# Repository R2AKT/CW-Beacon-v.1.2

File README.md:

# CW_Beacon
2-х канальный QPR CW автономный маяк (возможна работа только одного канала).
В основе Arduino Nano, генераторная часть построена на кварцевом резонаторе
и стандартной логике. В качестве оконечного каскада используется магистральный
шинный формирователь. На выходе стоят ФНЧ 7-го порядка.

Маяк передаёт заранее заложенное сообщение, при наличии термодатчика DS18B20 и/или резистивного 
делителя напряжения можно добавлять измеренные значения в сообщение.

Подробное описание можно найти на сайте <a href="https://r2akt.ru/%d0%bf%d1%80%d0%be%d0%b5%d0%ba%d1%82%d1%8b/%d0%b0%d0%b2%d1%82%d0%be%d0%bd%d0%be%d0%bc%d0%bd%d1%8b%d0%b9-cw-%d0%bc%d0%b0%d1%8f%d0%ba-%d0%bd%d0%b0-%d0%b1%d0%b0%d0%b7%d0%b5-arduino-nano/" target=_blank>https://r2akt.ru/%d0%bf%d1%80%d0%be%d0%b5%d0%ba%d1%82%d1%8b/%d0%b0%d0%b2%d1%82%d0%be%d0%bd%d0%be%d0%bc%d0%bd%d1%8b%d0%b9-cw-%d0%bc%d0%b0%d1%8f%d0%ba-%d0%bd%d0%b0-%d0%b1%d0%b0%d0%b7%d0%b5-arduino-nano/</a>

## Баги и обратная связь
При нахождении багов создавайте **Issue**.  
Библиотека открыта для доработки и ваших **Pull Request**'ов!

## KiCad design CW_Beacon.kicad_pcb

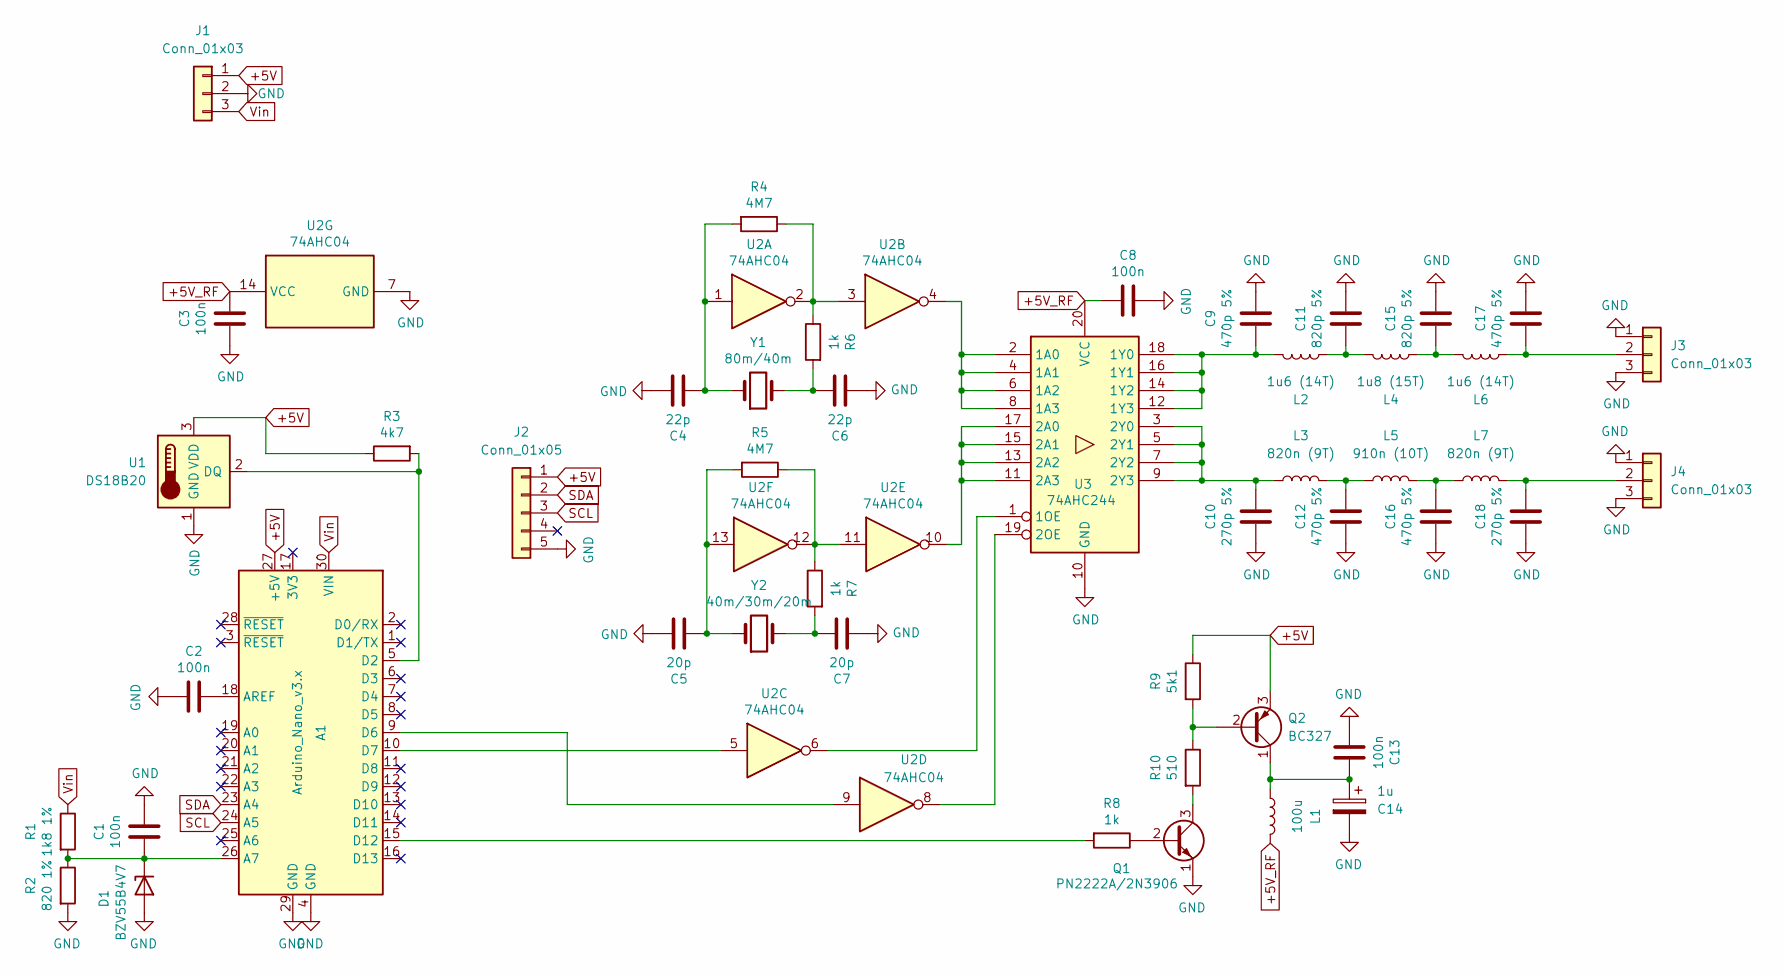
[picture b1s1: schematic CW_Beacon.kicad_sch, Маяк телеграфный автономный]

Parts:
A1: Arduino_Nano_v3.x; Arduino_Nano
C1, C2, C3, C8, C13: 100n; C_0805_2012Metric_Pad1.18x1.45mm_HandSolder
C4, C6: 22p; C_0805_2012Metric_Pad1.18x1.45mm_HandSolder
C5, C7: 20p; C_0805_2012Metric_Pad1.18x1.45mm_HandSolder
C9, C12, C16, C17: 470p 5%; C_0805_2012Metric_Pad1.18x1.45mm_HandSolder
C10, C18: 270p 5%; C_0805_2012Metric_Pad1.18x1.45mm_HandSolder
C11, C15: 820p 5%; C_0805_2012Metric_Pad1.18x1.45mm_HandSolder
C14: 1u; CP_Radial_D6.3mm_P2.50mm
D1: BZV55B4V7; D_MiniMELF
J1, J3, J4: Conn_01x03; PinSocket_1x03_P2.54mm_Vertical
J2: Conn_01x05; PinHeader_1x05_P2.54mm_Vertical
L1: 100u; L_Radial_D8.7mm_P5.00mm_Fastron_07HCP
L2, L6: 1u6 (14T); TNT_Variable_Induction_7x7
L3, L7: 820n (9T); TNT_Variable_Induction_7x7
L4: 1u8 (15T); TNT_Variable_Induction_7x7
L5: 910n (10T); TNT_Variable_Induction_7x7
Q1: PN2222A/2N3906; TO-92_Inline
Q2: BC327; TO-92_Inline
R1: 1k8 1%; R_0805_2012Metric_Pad1.20x1.40mm_HandSolder
R2: 820 1%; R_0805_2012Metric_Pad1.20x1.40mm_HandSolder
R3: 4k7; R_0805_2012Metric_Pad1.20x1.40mm_HandSolder
R4, R5: 4M7; R_0805_2012Metric_Pad1.20x1.40mm_HandSolder
R6, R7, R8: 1k; R_0805_2012Metric_Pad1.20x1.40mm_HandSolder
R9: 5k1; R_0805_2012Metric_Pad1.20x1.40mm_HandSolder
R10: 510; R_0805_2012Metric_Pad1.20x1.40mm_HandSolder
U1: DS18B20; TO-92_Inline
U2: 74AHC04; SOIC-14_3.9x8.7mm_P1.27mm
U3: 74AHC244; SO-20_12.8x7.5mm_P1.27mm
Y1: 80m/40m; Crystal_HC49-U_Vertical
Y2: 40m/30m/20m; Crystal_HC49-U_Vertical

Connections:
+5V: A1.27 (+5V), J1.1, J2.1, Q2.3 (E), R3.1, R9.1, U1.3 (VDD)
+5V_RF: C3.1, C8.1, L1.2, U2.14 (VCC), U3.20 (VCC)
GND: A1.4 (GND), A1.29 (GND), C1.2, C2.2, C3.2, C4.1, C5.1, C6.2, C7.2, C8.2, C9.1, C10.1, C11.1, C12.1, C13.2, C14.2, C15.1, C16.1, C17.1, C18.1, D1.2 (A), J1.2, J2.5, J3.1, J3.3, J4.1, J4.3, Q1.1 (E), R2.2, U1.1 (GND), U2.7 (GND), U3.10 (GND)
unnamed: A1.26 (A7), C1.1, D1.1 (K), R1.2, R2.1
unnamed: A1.18 (AREF), C2.1
unnamed: A1.5 (D2), R3.2, U1.2 (DQ)
unnamed: A1.9 (D6), U2.9
unnamed: A1.10 (D7), U2.5
unnamed: A1.15 (D12), R8.2
unnamed: C4.2, R4.2, U2.1, Y1.1
unnamed: C5.2, R5.2, U2.13, Y2.1
unnamed: C6.1, R6.2, Y1.2
unnamed: C7.1, R7.2, Y2.2
unnamed: C11.2, L2.2, L4.1
unnamed: C12.2, L3.2, L5.1
unnamed: C15.2, L4.2, L6.1
unnamed: C16.2, L5.2, L7.1
unnamed: C17.2, J3.2, L6.2
unnamed: C18.2, J4.2, L7.2
unnamed: Q1.2 (B), R8.1
unnamed: Q1.3 (C), R10.2
unnamed: Q2.2 (B), R9.2, R10.1
unnamed: C13.1, C14.1, L1.1, Q2.1 (C)
unnamed: R4.1, R6.1, U2.2, U2.3
unnamed: R5.1, R7.1, U2.11, U2.12
unnamed: U2.4, U3.2 (1A0), U3.4 (1A1), U3.6 (1A2), U3.8 (1A3)
unnamed: U2.6, U3.1 (1OE)
unnamed: C9.2, L2.1, U3.12 (1Y3), U3.14 (1Y2), U3.16 (1Y1), U3.18 (1Y0)
unnamed: U2.10, U3.11 (2A3), U3.13 (2A2), U3.15 (2A1), U3.17 (2A0)
unnamed: U2.8, U3.19 (2OE)
unnamed: C10.2, L3.1, U3.3 (2Y0), U3.5 (2Y1), U3.7 (2Y2), U3.9 (2Y3)
SCL: A1.24 (A5), J2.3
SDA: A1.23 (A4), J2.2
Vin: A1.30 (VIN), J1.3, R1.1

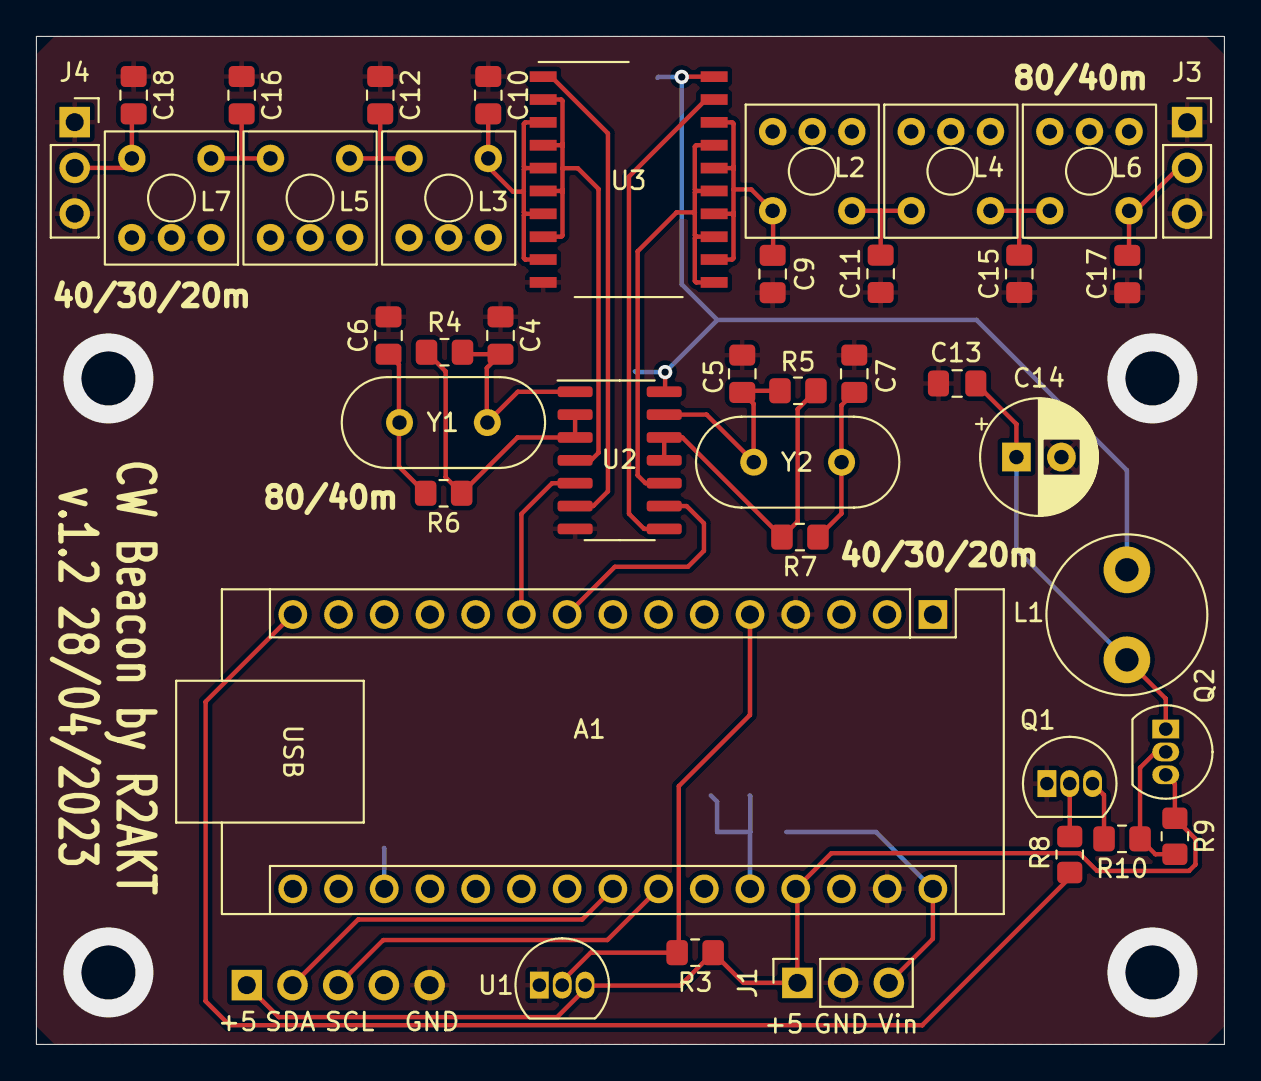
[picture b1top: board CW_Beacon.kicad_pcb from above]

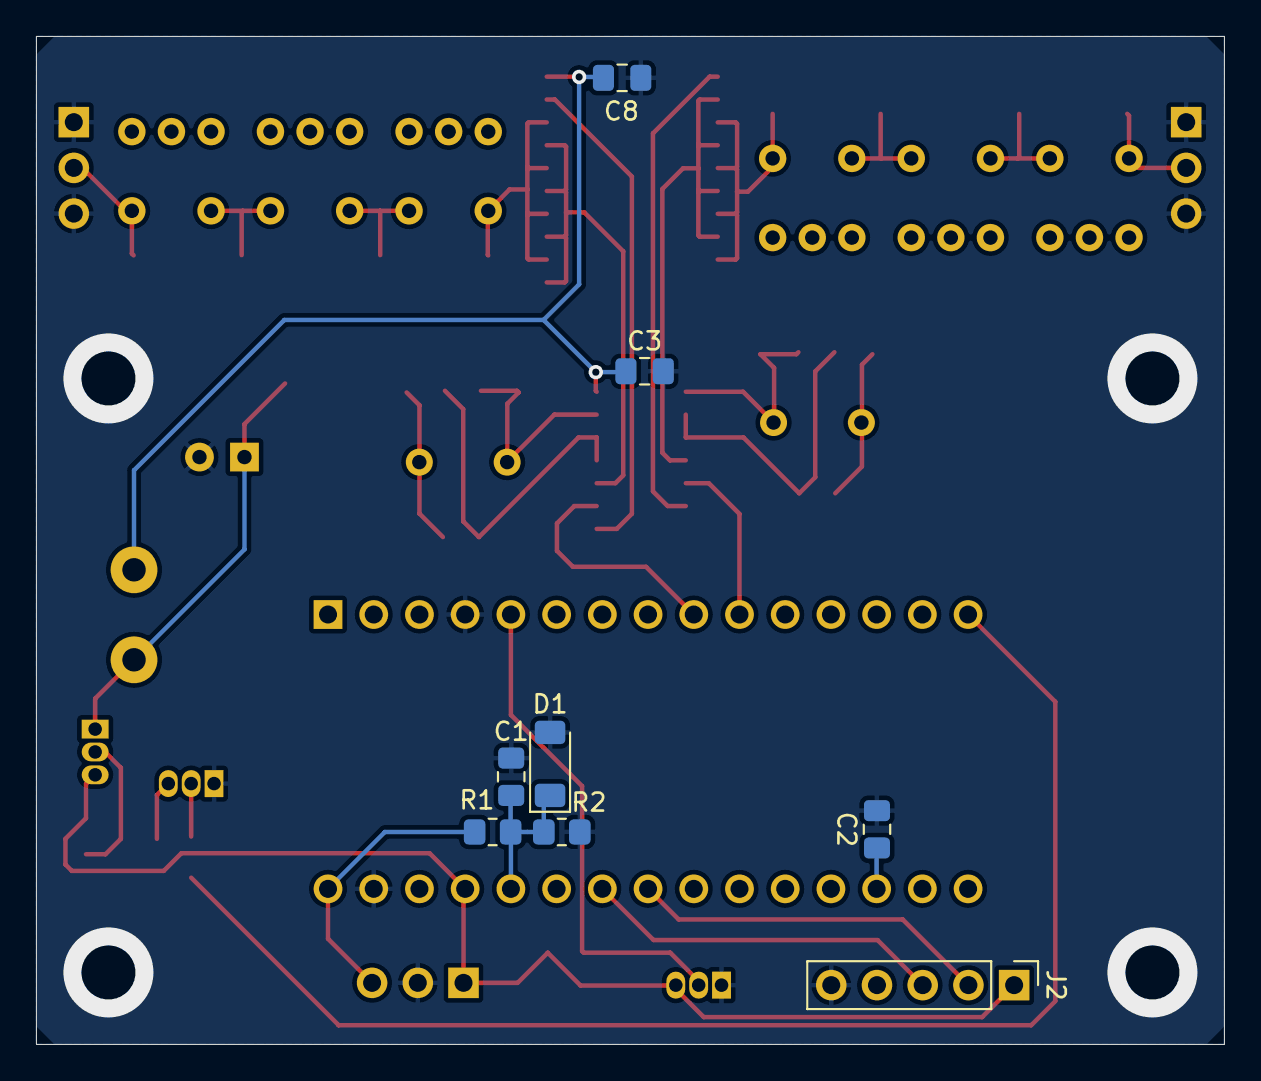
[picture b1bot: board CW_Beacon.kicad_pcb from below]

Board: 2 copper layers, 66.0 x 56.0 mm, 48 parts (8 on the bottom side), 34 nets.

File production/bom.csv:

Designator,Footprint,Quantity,Value,LCSC Part #
A1,Arduino_Nano,1,Arduino_Nano_v3.x,
"C1, C13, C2, C3, C8",C_0805_2012Metric_Pad1.18x1.45mm_HandSolder,5,100n,
"C10, C18",C_0805_2012Metric_Pad1.18x1.45mm_HandSolder,2,270p 5%,
"C11, C15",C_0805_2012Metric_Pad1.18x1.45mm_HandSolder,2,820p 5%,
"C12, C16, C17, C9",C_0805_2012Metric_Pad1.18x1.45mm_HandSolder,4,470p 5%,
C14,CP_Radial_D6.3mm_P2.50mm,1,1u,
"C4, C6",C_0805_2012Metric_Pad1.18x1.45mm_HandSolder,2,22p,
"C5, C7",C_0805_2012Metric_Pad1.18x1.45mm_HandSolder,2,20p,
D1,D_MiniMELF,1,BZV55B4V7,
"J1, J3, J4",PinSocket_1x03_P2.54mm_Vertical,3,Conn_01x03,
J2,PinHeader_1x05_P2.54mm_Vertical,1,Conn_01x05,
L1,L_Radial_D8.7mm_P5.00mm_Fastron_07HCP,1,100u,
"L2, L6",TNT_Variable_Induction_7x7,2,1u6 (14T),
"L3, L7",TNT_Variable_Induction_7x7,2,820n (9T),
L4,TNT_Variable_Induction_7x7,1,1u8 (15T),
L5,TNT_Variable_Induction_7x7,1,910n (10T),
Q1,TO-92_Inline,1,PN2222A/2N3906,
Q2,TO-92_Inline,1,BC327,
R1,R_0805_2012Metric_Pad1.20x1.40mm_HandSolder,1,1k8 1%,
"R10, R6, R7, R8",R_0805_2012Metric_Pad1.20x1.40mm_HandSolder,4,1k,
R2,R_0805_2012Metric_Pad1.20x1.40mm_HandSolder,1,820 1%,
"R3, R9",R_0805_2012Metric_Pad1.20x1.40mm_HandSolder,2,4k7,
"R4, R5",R_0805_2012Metric_Pad1.20x1.40mm_HandSolder,2,4M7,
U1,TO-92_Inline,1,DS18B20,
U2,SOIC-14_3.9x8.7mm_P1.27mm,1,74AHC04,
U3,SO-20_12.8x7.5mm_P1.27mm,1,74AHC244,
Y1,Crystal_HC49-U_Vertical,1,80m/40m,
Y2,Crystal_HC49-U_Vertical,1,40m/30m/20m,

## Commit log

2024-05-19 Upload files

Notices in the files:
README.md:
License: MIT
